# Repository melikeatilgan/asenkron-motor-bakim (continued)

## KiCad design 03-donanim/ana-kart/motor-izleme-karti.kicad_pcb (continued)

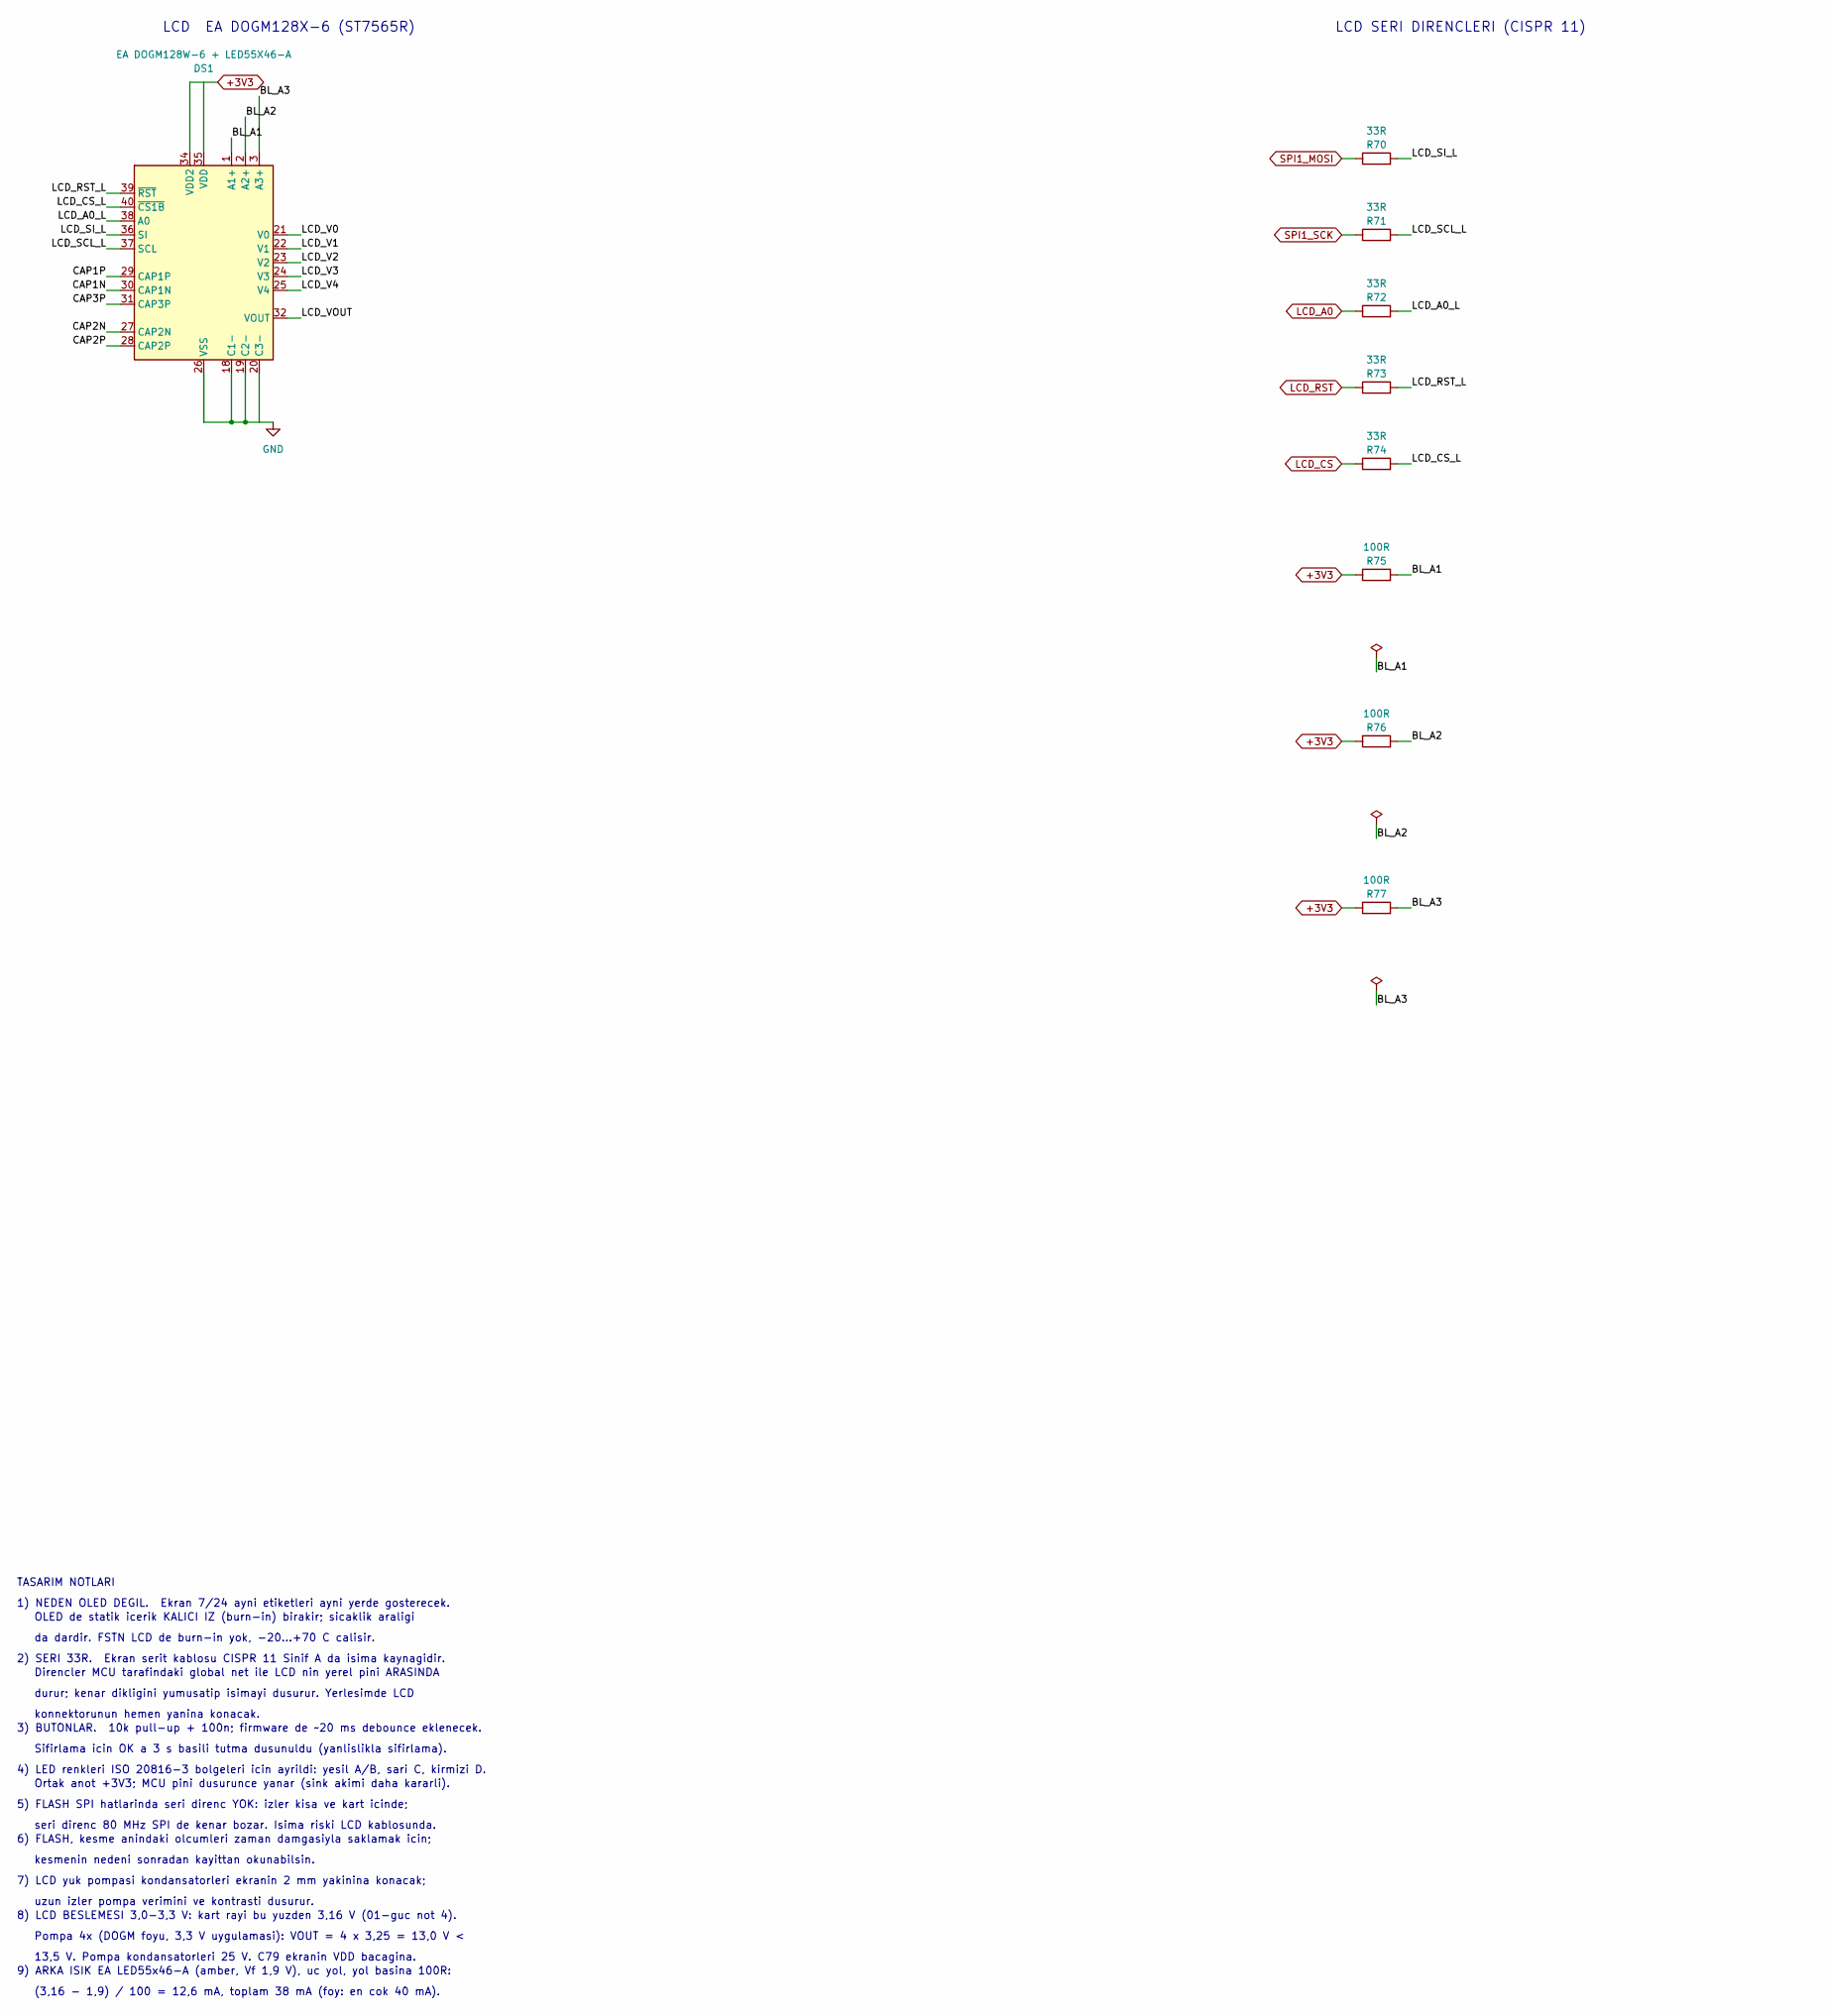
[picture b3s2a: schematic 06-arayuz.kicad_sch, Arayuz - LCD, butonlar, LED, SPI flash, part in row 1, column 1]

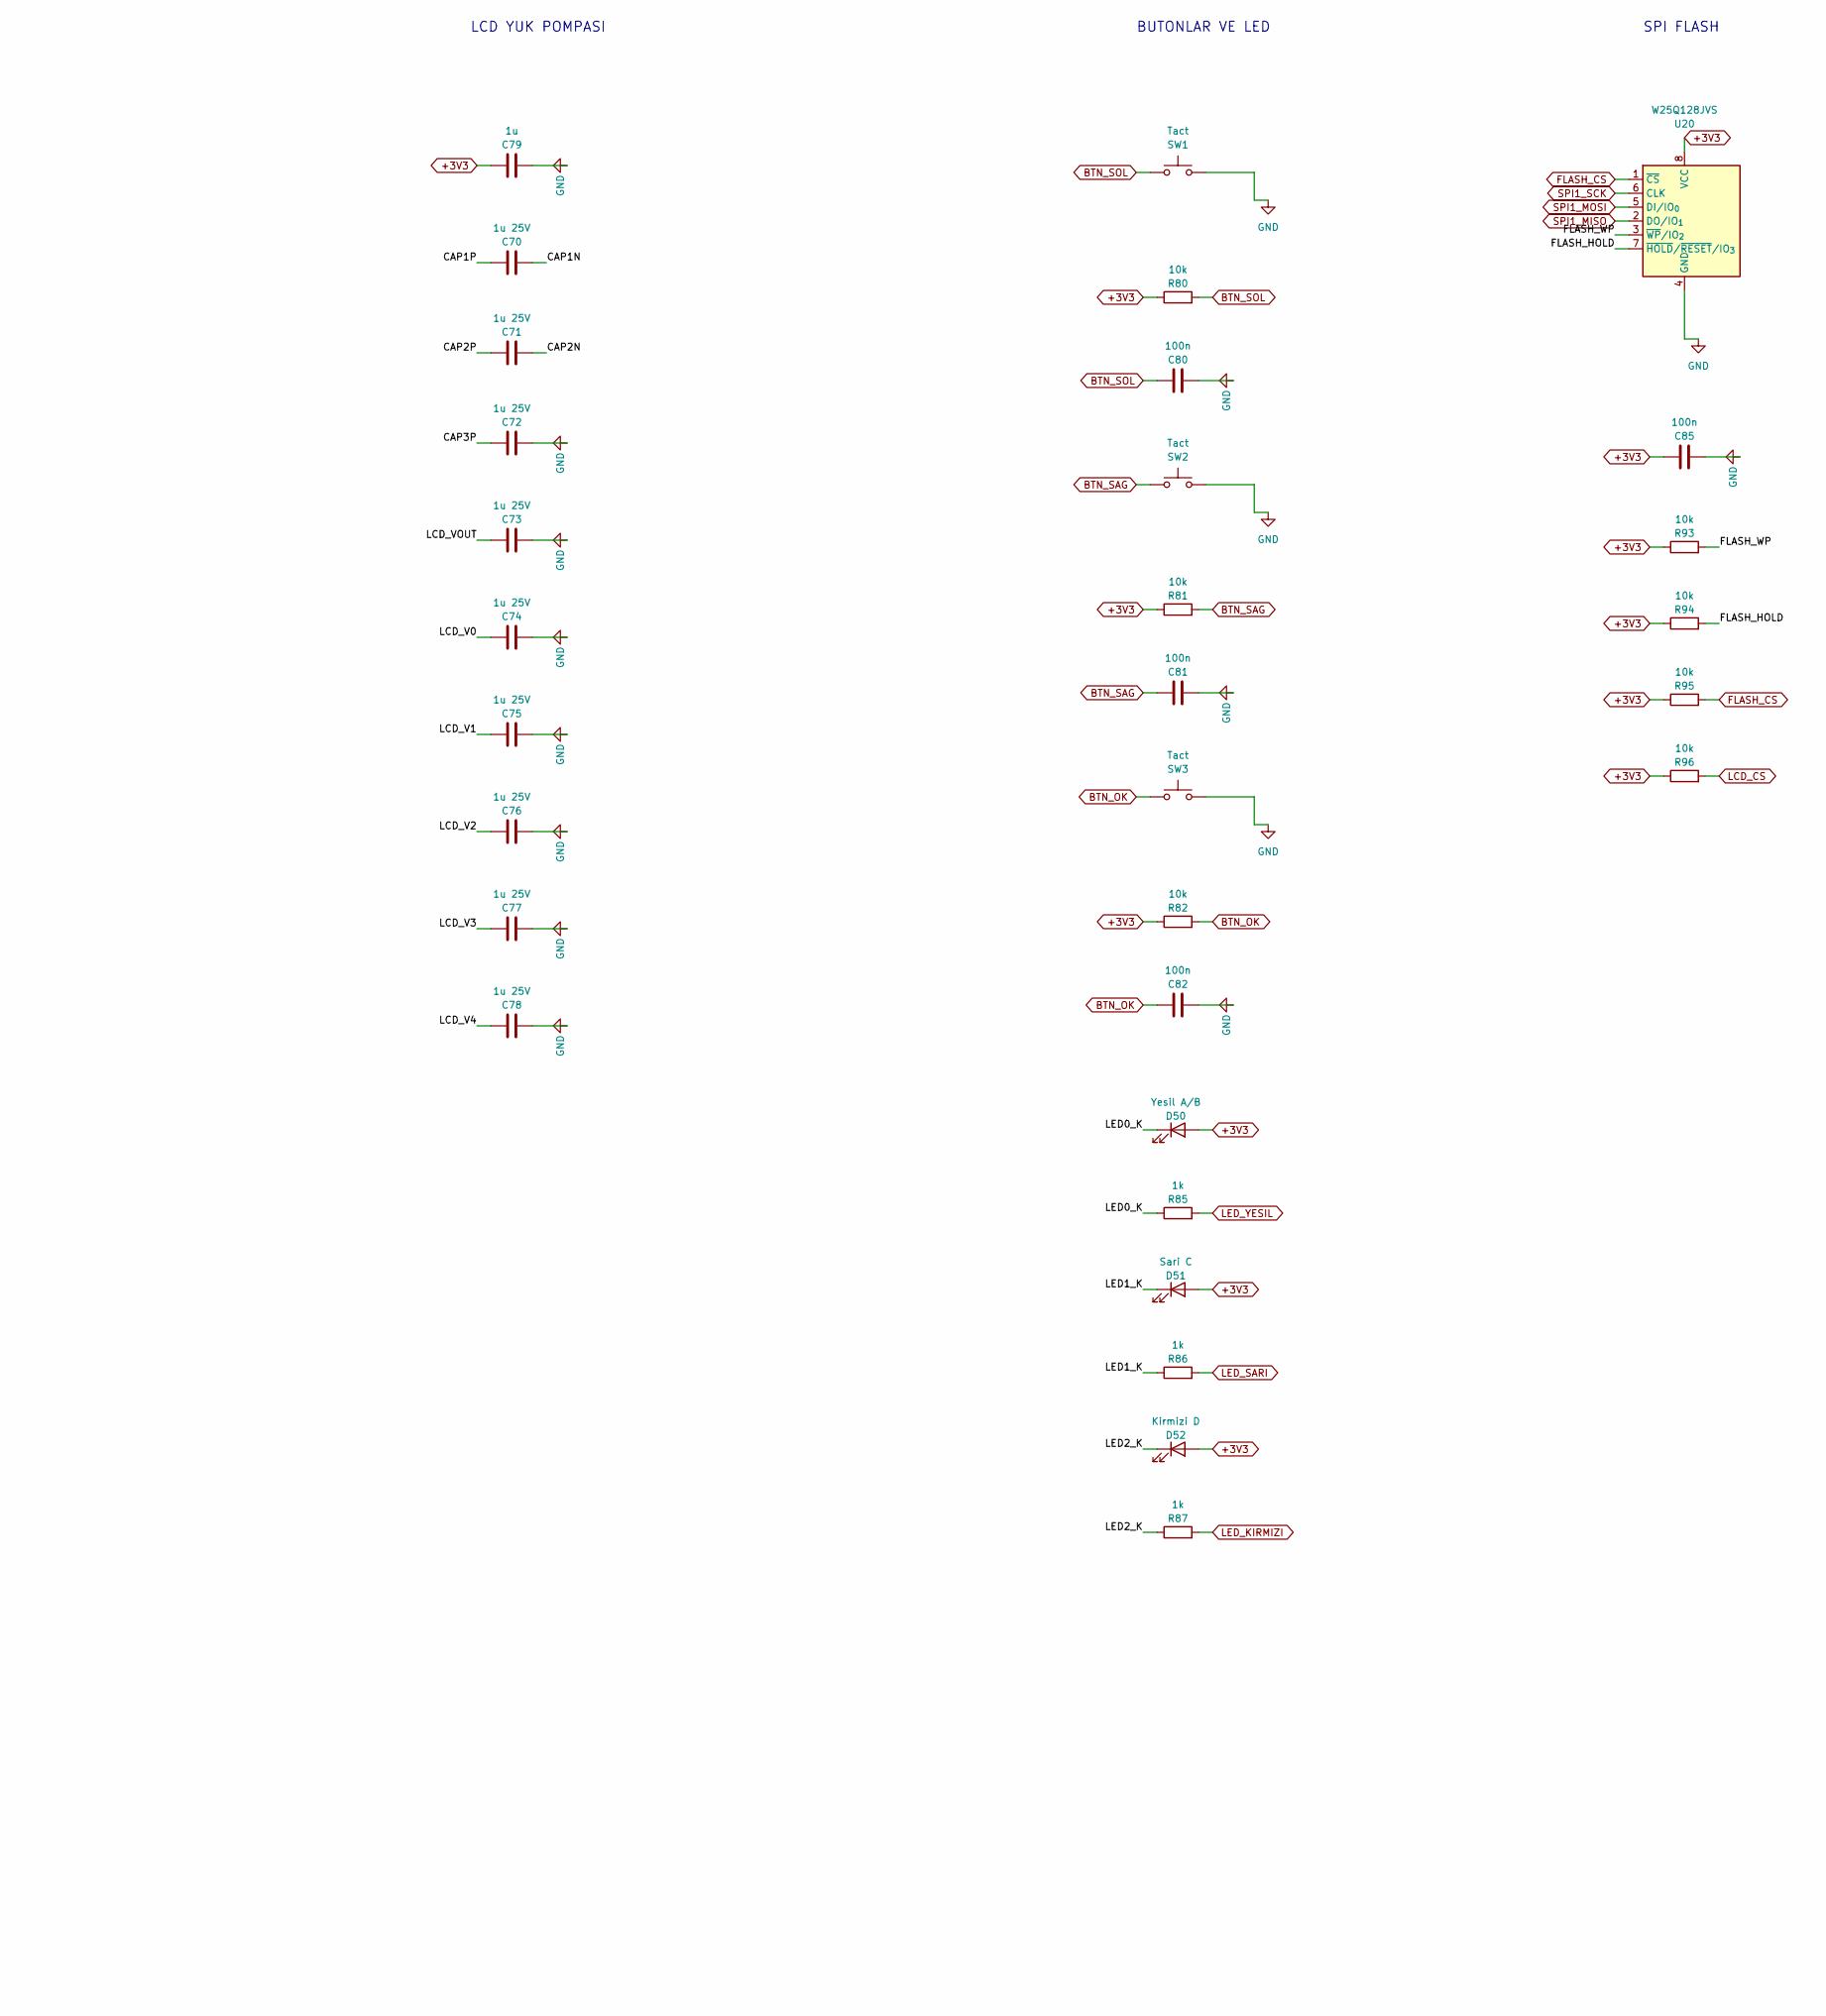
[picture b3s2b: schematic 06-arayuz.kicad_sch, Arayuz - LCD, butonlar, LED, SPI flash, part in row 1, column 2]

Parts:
C70, C71, C72, C73, C74, C75, C76, C77, C78: 1u 25V; C_0805_2012Metric
C79: 1u; C_0805_2012Metric
C80, C81, C82, C85: 100n; C_0805_2012Metric
D50: Yesil A/B; LED_0805_2012Metric
D51: Sari C; LED_0805_2012Metric
D52: Kirmizi D; LED_0805_2012Metric
DS1: EA DOGM128W-6 + LED55X46-A; EA_DOGM128-6
R70, R71, R72, R73, R74: 33R; R_0805_2012Metric
R75, R76, R77: 100R; R_0805_2012Metric
R80, R81, R82, R93, R94, R95, R96: 10k; R_0805_2012Metric
R85, R86, R87: 1k; R_0805_2012Metric
SW1, SW2, SW3: Tact; SW_SPST_PTS645Sx43SMTR92
U20: W25Q128JVS; SOIC-8_3.9x4.9mm_P1.27mm

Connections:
+3V3: C79.1, C85.1, D50.2 (A), D51.2 (A), D52.2 (A), DS1.34 (VDD2), DS1.35 (VDD), R75.1, R76.1, R77.1, R80.1, R81.1, R82.1, R93.1, R94.1, R95.1, R96.1, U20.8 (VCC); also elsewhere on the board
/06-arayuz/BL_A1: DS1.1 (A1+), R75.2
/06-arayuz/BL_A2: DS1.2 (A2+), R76.2
/06-arayuz/BL_A3: DS1.3 (A3+), R77.2
/06-arayuz/CAP1N: C70.2, DS1.30 (CAP1N)
/06-arayuz/CAP1P: C70.1, DS1.29 (CAP1P)
/06-arayuz/CAP2N: C71.2, DS1.27 (CAP2N)
/06-arayuz/CAP2P: C71.1, DS1.28 (CAP2P)
/06-arayuz/CAP3P: C72.1, DS1.31 (CAP3P)
/06-arayuz/FLASH_HOLD: R94.2, U20.7 (~HOLD/~RESET/IO_{3})
/06-arayuz/FLASH_WP: R93.2, U20.3 (~WP/IO_{2})
/06-arayuz/LCD_A0_L: DS1.38 (A0), R72.2
/06-arayuz/LCD_CS_L: DS1.40 (~CS1B), R74.2
/06-arayuz/LCD_RST_L: DS1.39 (~RST), R73.2
/06-arayuz/LCD_SCL_L: DS1.37 (SCL), R71.2
/06-arayuz/LCD_SI_L: DS1.36 (SI), R70.2
/06-arayuz/LCD_V0: C74.1, DS1.21 (V0)
/06-arayuz/LCD_V1: C75.1, DS1.22 (V1)
/06-arayuz/LCD_V2: C76.1, DS1.23 (V2)
/06-arayuz/LCD_V3: C77.1, DS1.24 (V3)
/06-arayuz/LCD_V4: C78.1, DS1.25 (V4)
/06-arayuz/LCD_VOUT: C73.1, DS1.32 (VOUT)
/06-arayuz/LED0_K: D50.1 (K), R85.1
/06-arayuz/LED1_K: D51.1 (K), R86.1
/06-arayuz/LED2_K: D52.1 (K), R87.1
BTN_OK: C82.1, R82.2, SW3.1; also elsewhere on the board
BTN_SAG: C81.1, R81.2, SW2.1; also elsewhere on the board
BTN_SOL: C80.1, R80.2, SW1.1; also elsewhere on the board
FLASH_CS: R95.2, U20.1 (~CS); also elsewhere on the board
GND: C72.2, C73.2, C74.2, C75.2, C76.2, C77.2, C78.2, C79.2, C80.2, C81.2, C82.2, C85.2, DS1.18 (C1-), DS1.19 (C2-), DS1.20 (C3-), DS1.26 (VSS), DS1.33 (VSS), SW1.2, SW2.2, SW3.2, U20.4 (GND); also elsewhere on the board
LCD_A0: R72.1; also elsewhere on the board
LCD_CS: R74.1, R96.2; also elsewhere on the board
LCD_RST: R73.1; also elsewhere on the board
LED_KIRMIZI: R87.2; also elsewhere on the board
LED_SARI: R86.2; also elsewhere on the board
LED_YESIL: R85.2; also elsewhere on the board
SPI1_MISO: U20.2 (DO/IO_{1}); also elsewhere on the board
SPI1_MOSI: R70.1, U20.5 (DI/IO_{0}); also elsewhere on the board
SPI1_SCK: R71.1, U20.6 (CLK); also elsewhere on the board

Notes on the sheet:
SPI FLASH
seri direnc 80 MHz SPI de kenar bozar. Isima riski LCD kablosunda.
TASARIM NOTLARI
3) BUTONLAR. 10k pull-up + 100n; firmware de ~20 ms debounce eklenecek.
uzun izler pompa verimini ve kontrasti dusurur.
7) LCD yuk pompasi kondansatorleri ekranin 2 mm yakinina konacak;
9) ARKA ISIK EA LED55x46-A (amber, Vf 1,9 V), uc yol, yol basina 100R:
13,5 V. Pompa kondansatorleri 25 V. C79 ekranin VDD bacagina.
1) NEDEN OLED DEGIL. Ekran 7/24 ayni etiketleri ayni yerde gosterecek.
LCD SERI DIRENCLERI (CISPR 11)
8) LCD BESLEMESI 3,0-3,3 V: kart rayi bu yuzden 3,16 V (01-guc not 4).
Ortak anot +3V3; MCU pini dusurunce yanar (sink akimi daha kararli).
LCD EA DOGM128X-6 (ST7565R)
Sifirlama icin OK a 3 s basili tutma dusunuldu (yanlislikla sifirlama).
Direncler MCU tarafindaki global net ile LCD nin yerel pini ARASINDA
konnektorunun hemen yanina konacak.
kesmenin nedeni sonradan kayittan okunabilsin.
5) FLASH SPI hatlarinda seri direnc YOK: izler kisa ve kart icinde;
Pompa 4x (DOGM foyu, 3,3 V uygulamasi): VOUT = 4 x 3,25 = 13,0 V <
LCD YUK POMPASI
BUTONLAR VE LED
4) LED renkleri ISO 20816-3 bolgeleri icin ayrildi: yesil A/B, sari C, kirmizi D.
2) SERI 33R. Ekran serit kablosu CISPR 11 Sinif A da isima kaynagidir.
durur; kenar dikligini yumusatip isimayi dusurur. Yerlesimde LCD
OLED de statik icerik KALICI IZ (burn-in) birakir; sicaklik araligi
6) FLASH, kesme anindaki olcumleri zaman damgasiyla saklamak icin;
(3,16 - 1,9) / 100 = 12,6 mA, toplam 38 mA (foy: en cok 40 mA).
da dardir. FSTN LCD de burn-in yok, -20...+70 C calisir.

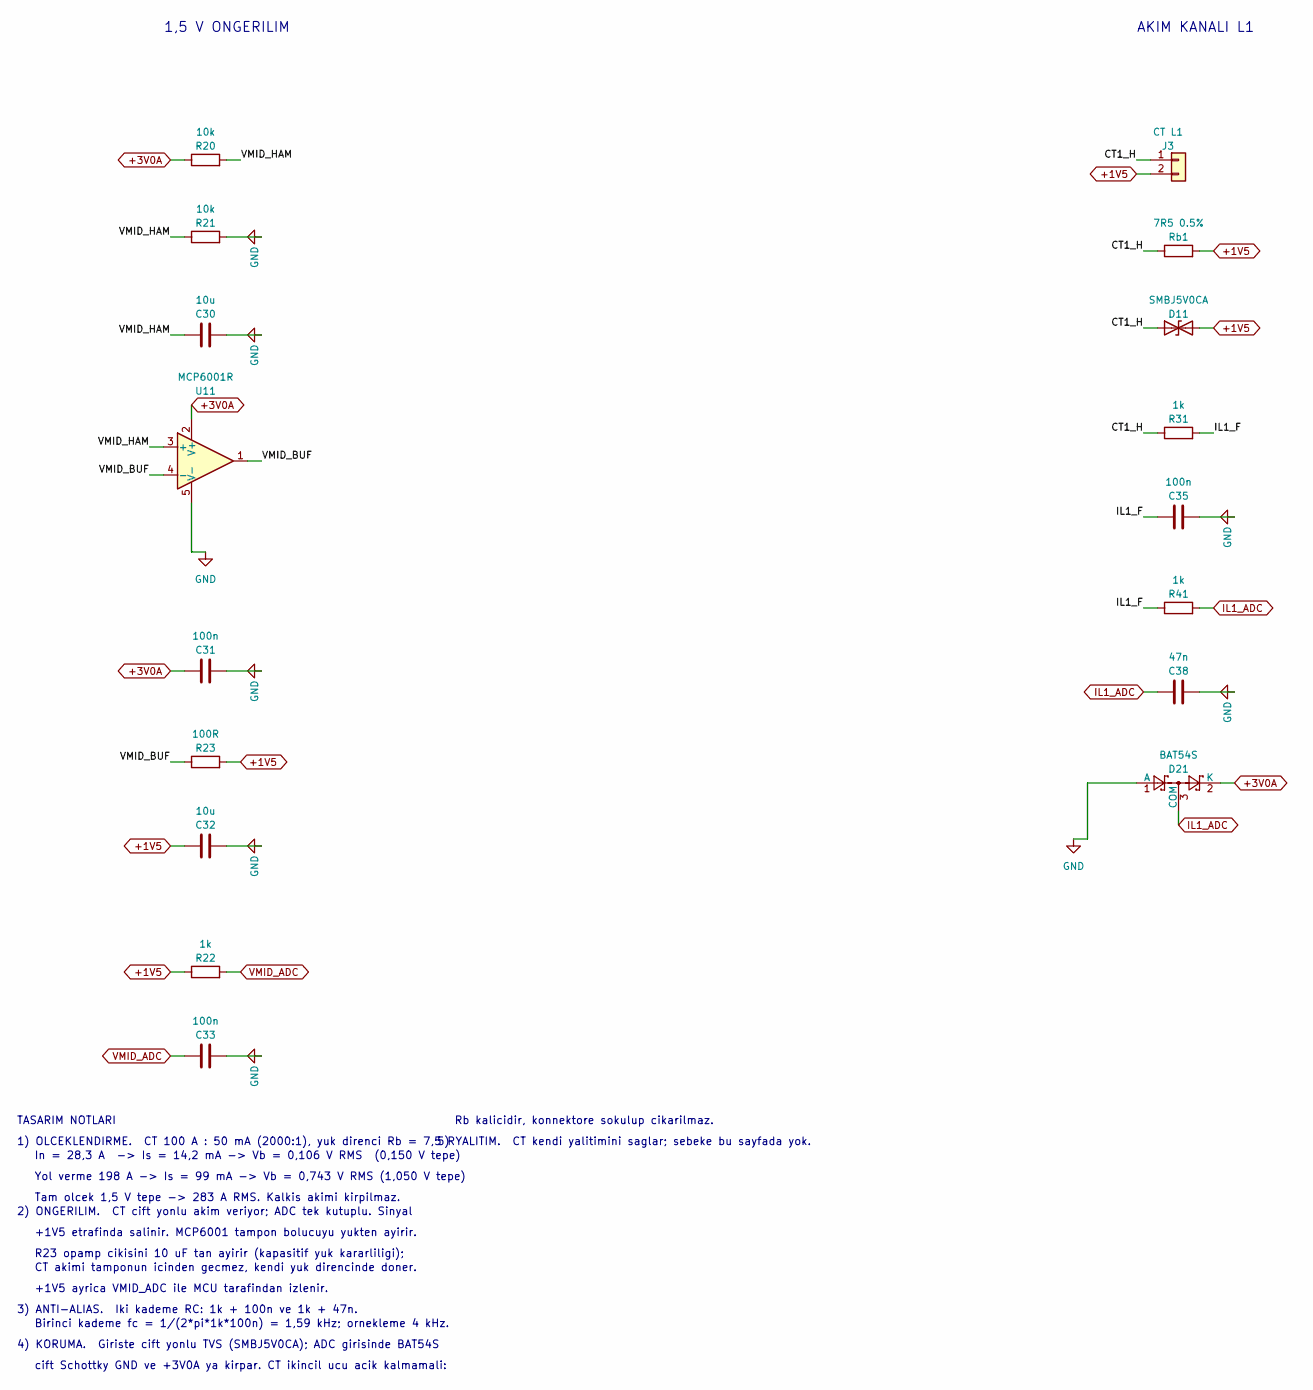
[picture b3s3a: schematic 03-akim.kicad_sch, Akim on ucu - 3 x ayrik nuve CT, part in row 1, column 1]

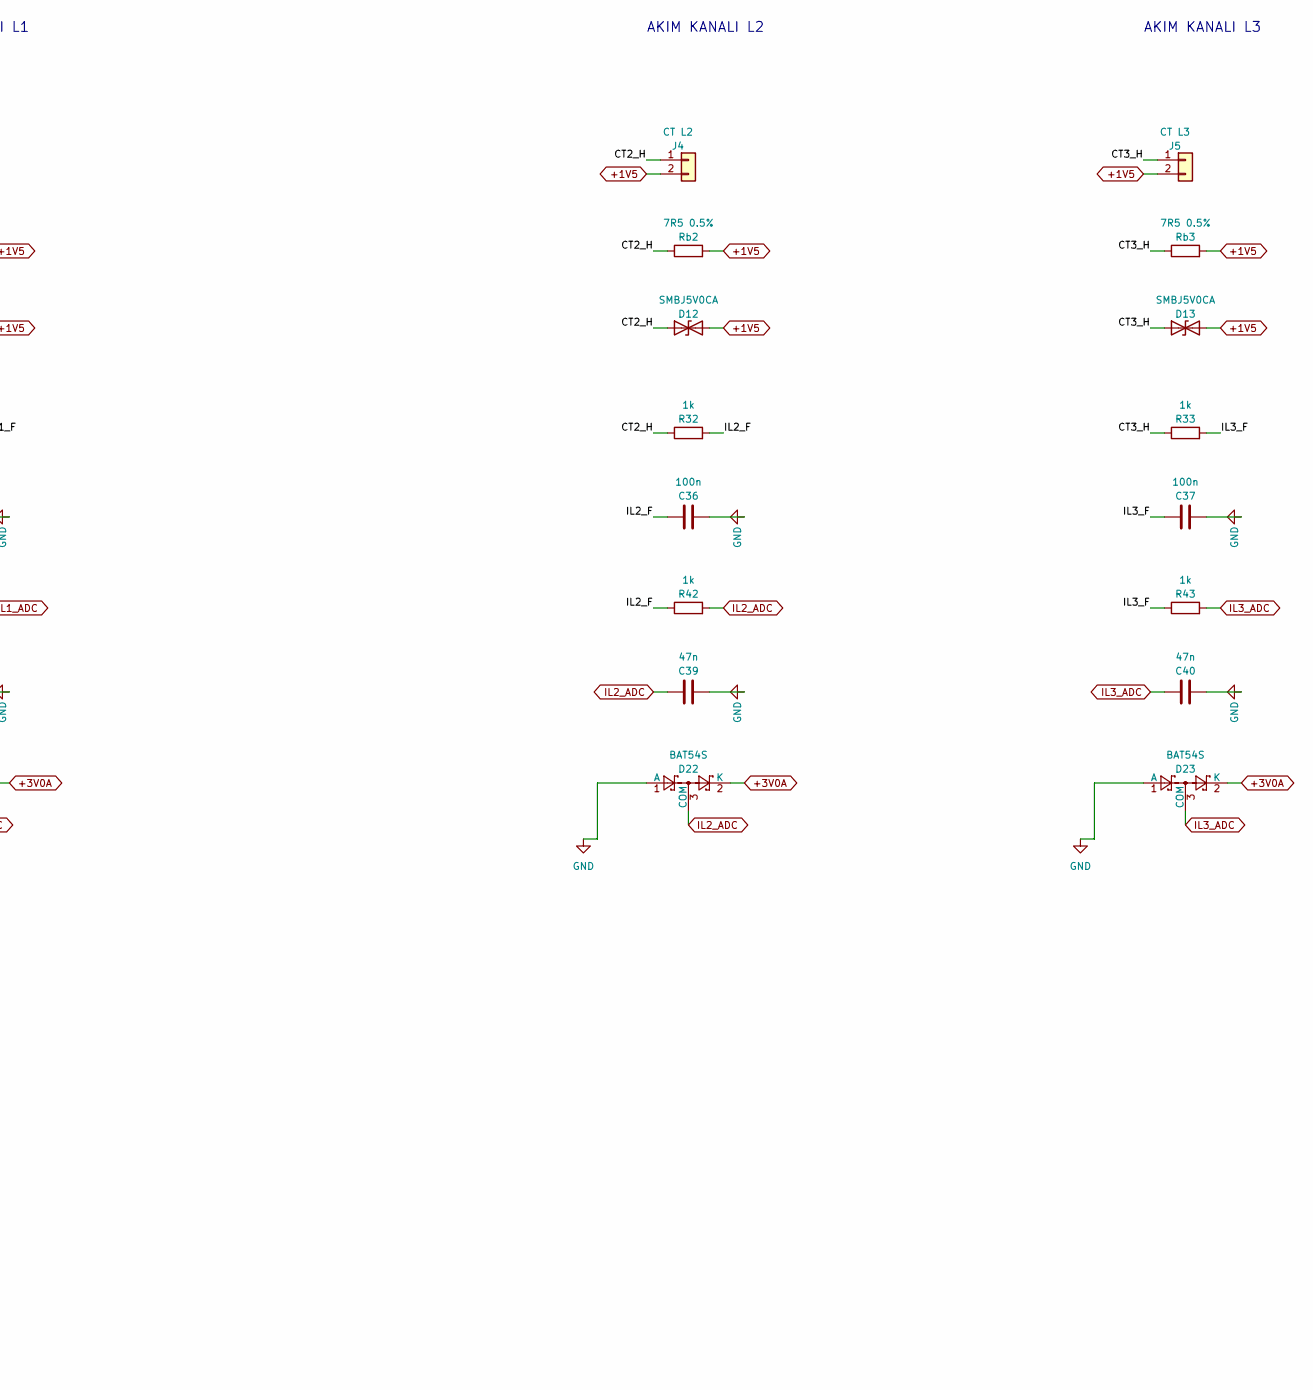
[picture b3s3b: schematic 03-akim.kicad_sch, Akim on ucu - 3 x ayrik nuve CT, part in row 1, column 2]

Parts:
C30, C32: 10u; C_1206_3216Metric
C31, C33, C35, C36, C37: 100n; C_0805_2012Metric
C38, C39, C40: 47n; C_0805_2012Metric
D11, D12, D13: SMBJ5V0CA; D_SMB
D21, D22, D23: BAT54S; SOT-23
J3: CT L1; TerminalBlock_Phoenix_MPT-0,5-2-2.54_1x02_P2.54mm_Horizontal
J4: CT L2; TerminalBlock_Phoenix_MPT-0,5-2-2.54_1x02_P2.54mm_Horizontal
J5: CT L3; TerminalBlock_Phoenix_MPT-0,5-2-2.54_1x02_P2.54mm_Horizontal
R20, R21: 10k; R_0805_2012Metric
R22, R31, R32, R33, R41, R42, R43: 1k; R_0805_2012Metric
R23: 100R; R_0805_2012Metric
Rb1, Rb2, Rb3: 7R5 0.5%; R_0805_2012Metric
U11: MCP6001R; SOT-23-5

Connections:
+1V5: C32.1, D11.2 (A2), D12.2 (A2), D13.2 (A2), J3.2, J4.2, J5.2, R22.1, R23.2, Rb1.2, Rb2.2, Rb3.2
+3V0A: C31.1, D21.2 (K), D22.2 (K), D23.2 (K), R20.1, U11.2 (V+); also elsewhere on the board
/03-akim/CT1_H: D11.1 (A1), J3.1, R31.1, Rb1.1
/03-akim/CT2_H: D12.1 (A1), J4.1, R32.1, Rb2.1
/03-akim/CT3_H: D13.1 (A1), J5.1, R33.1, Rb3.1
/03-akim/IL1_F: C35.1, R31.2, R41.1
/03-akim/IL2_F: C36.1, R32.2, R42.1
/03-akim/IL3_F: C37.1, R33.2, R43.1
/03-akim/VMID_BUF: R23.1, U11.1, U11.4 (-)
/03-akim/VMID_HAM: C30.1, R20.2, R21.1, U11.3 (+)
GND: C30.2, C31.2, C32.2, C33.2, C35.2, C36.2, C37.2, C38.2, C39.2, C40.2, D21.1 (A), D22.1 (A), D23.1 (A), R21.2, U11.5 (V-); also elsewhere on the board
IL1_ADC: C38.1, D21.3 (COM), R41.2; also elsewhere on the board
IL2_ADC: C39.1, D22.3 (COM), R42.2; also elsewhere on the board
IL3_ADC: C40.1, D23.3 (COM), R43.2; also elsewhere on the board
VMID_ADC: C33.1, R22.2; also elsewhere on the board

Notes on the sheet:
Yol verme 198 A -> Is = 99 mA -> Vb = 0,743 V RMS (1,050 V tepe)
In = 28,3 A -> Is = 14,2 mA -> Vb = 0,106 V RMS (0,150 V tepe)
+1V5 etrafinda salinir. MCP6001 tampon bolucuyu yukten ayirir.
AKIM KANALI L1
cift Schottky GND ve +3V0A ya kirpar. CT ikincil ucu acik kalmamali:
AKIM KANALI L2
Tam olcek 1,5 V tepe -> 283 A RMS. Kalkis akimi kirpilmaz.
2) ONGERILIM. CT cift yonlu akim veriyor; ADC tek kutuplu. Sinyal
Rb kalicidir, konnektore sokulup cikarilmaz.
Birinci kademe fc = 1/(2*pi*1k*100n) = 1,59 kHz; ornekleme 4 kHz.
3) ANTI-ALIAS. Iki kademe RC: 1k + 100n ve 1k + 47n.
4) KORUMA. Giriste cift yonlu TVS (SMBJ5V0CA); ADC girisinde BAT54S
+1V5 ayrica VMID_ADC ile MCU tarafindan izlenir.
1,5 V ONGERILIM
5) YALITIM. CT kendi yalitimini saglar; sebeke bu sayfada yok.
1) OLCEKLENDIRME. CT 100 A : 50 mA (2000:1), yuk direnci Rb = 7,5 R
TASARIM NOTLARI
CT akimi tamponun icinden gecmez, kendi yuk direncinde doner.
R23 opamp cikisini 10 uF tan ayirir (kapasitif yuk kararliligi);
AKIM KANALI L3

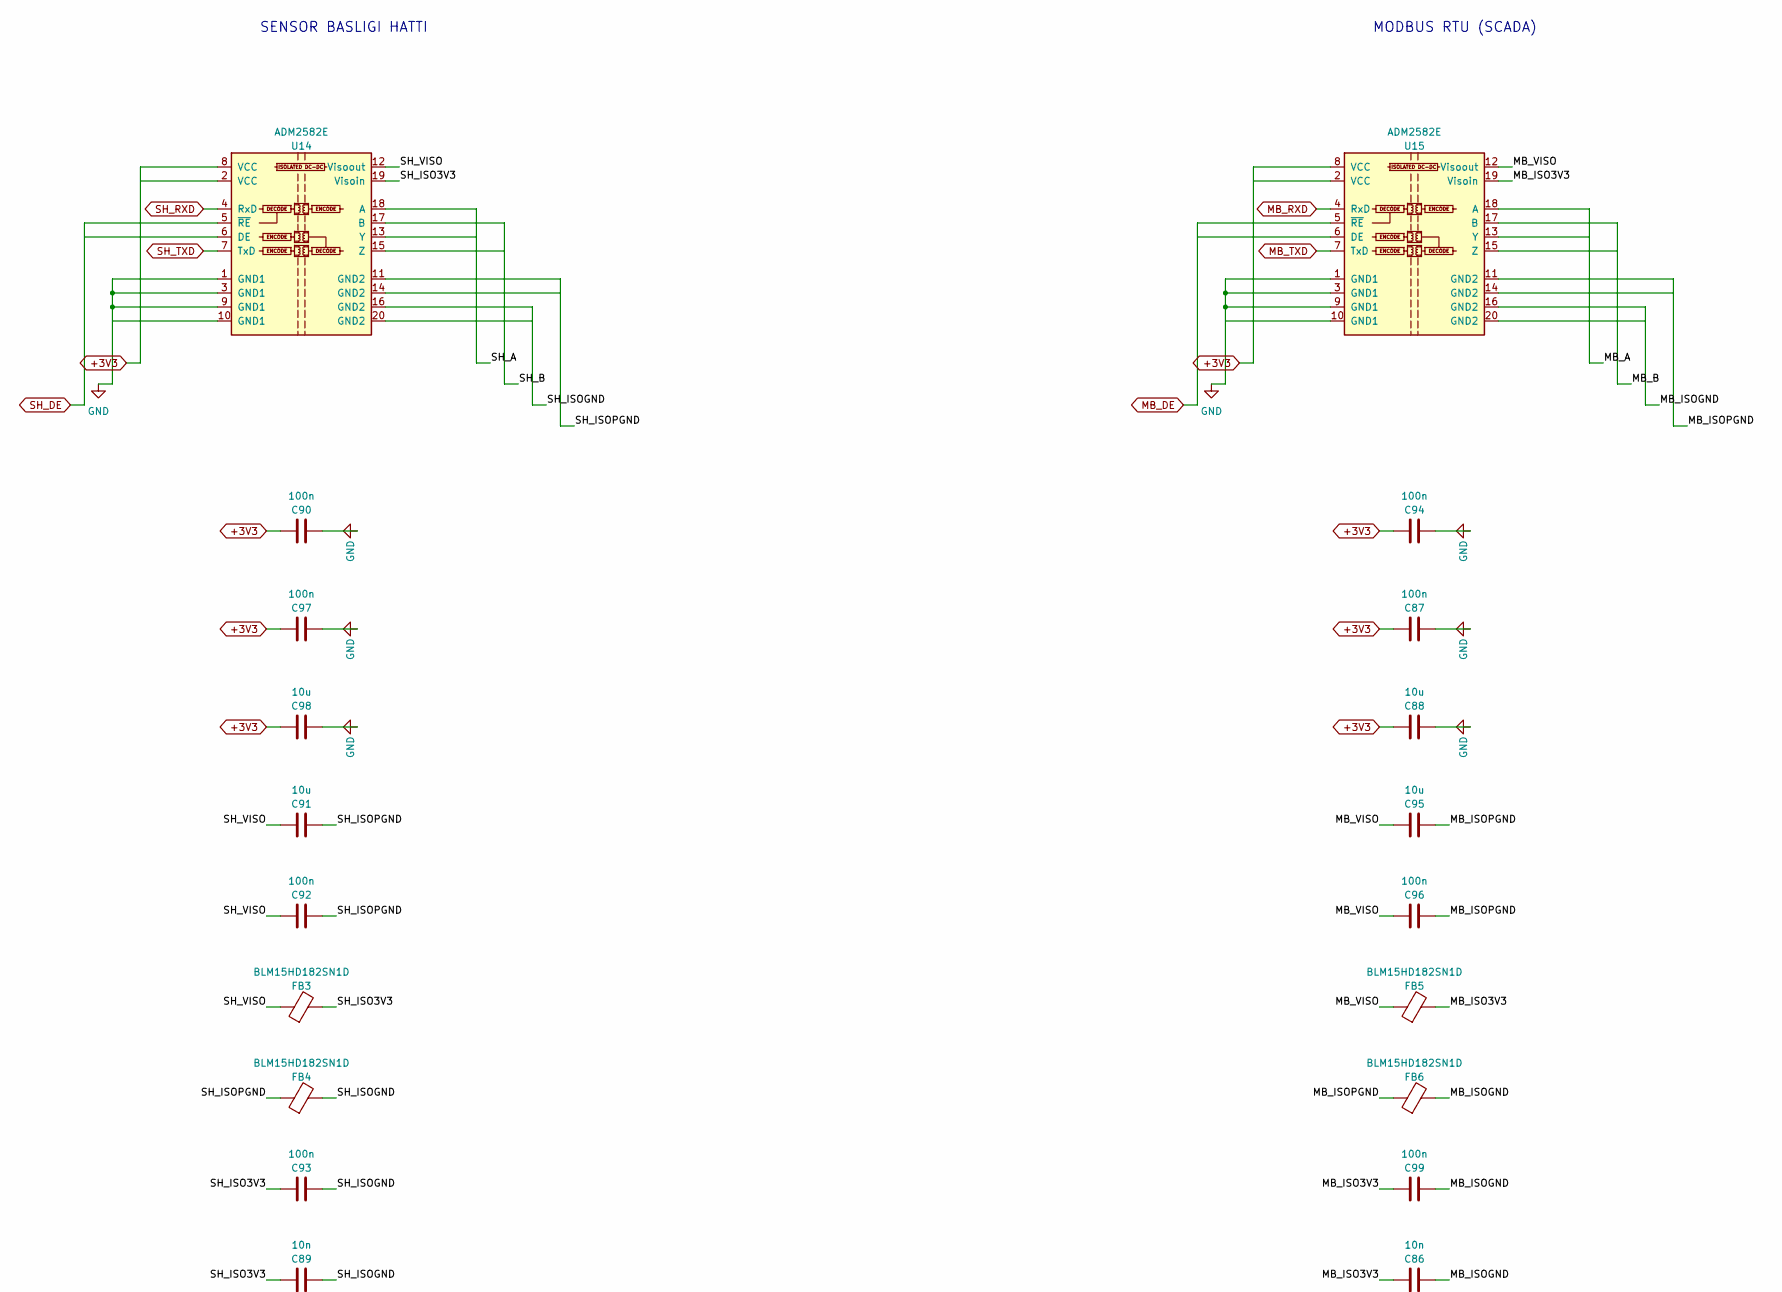
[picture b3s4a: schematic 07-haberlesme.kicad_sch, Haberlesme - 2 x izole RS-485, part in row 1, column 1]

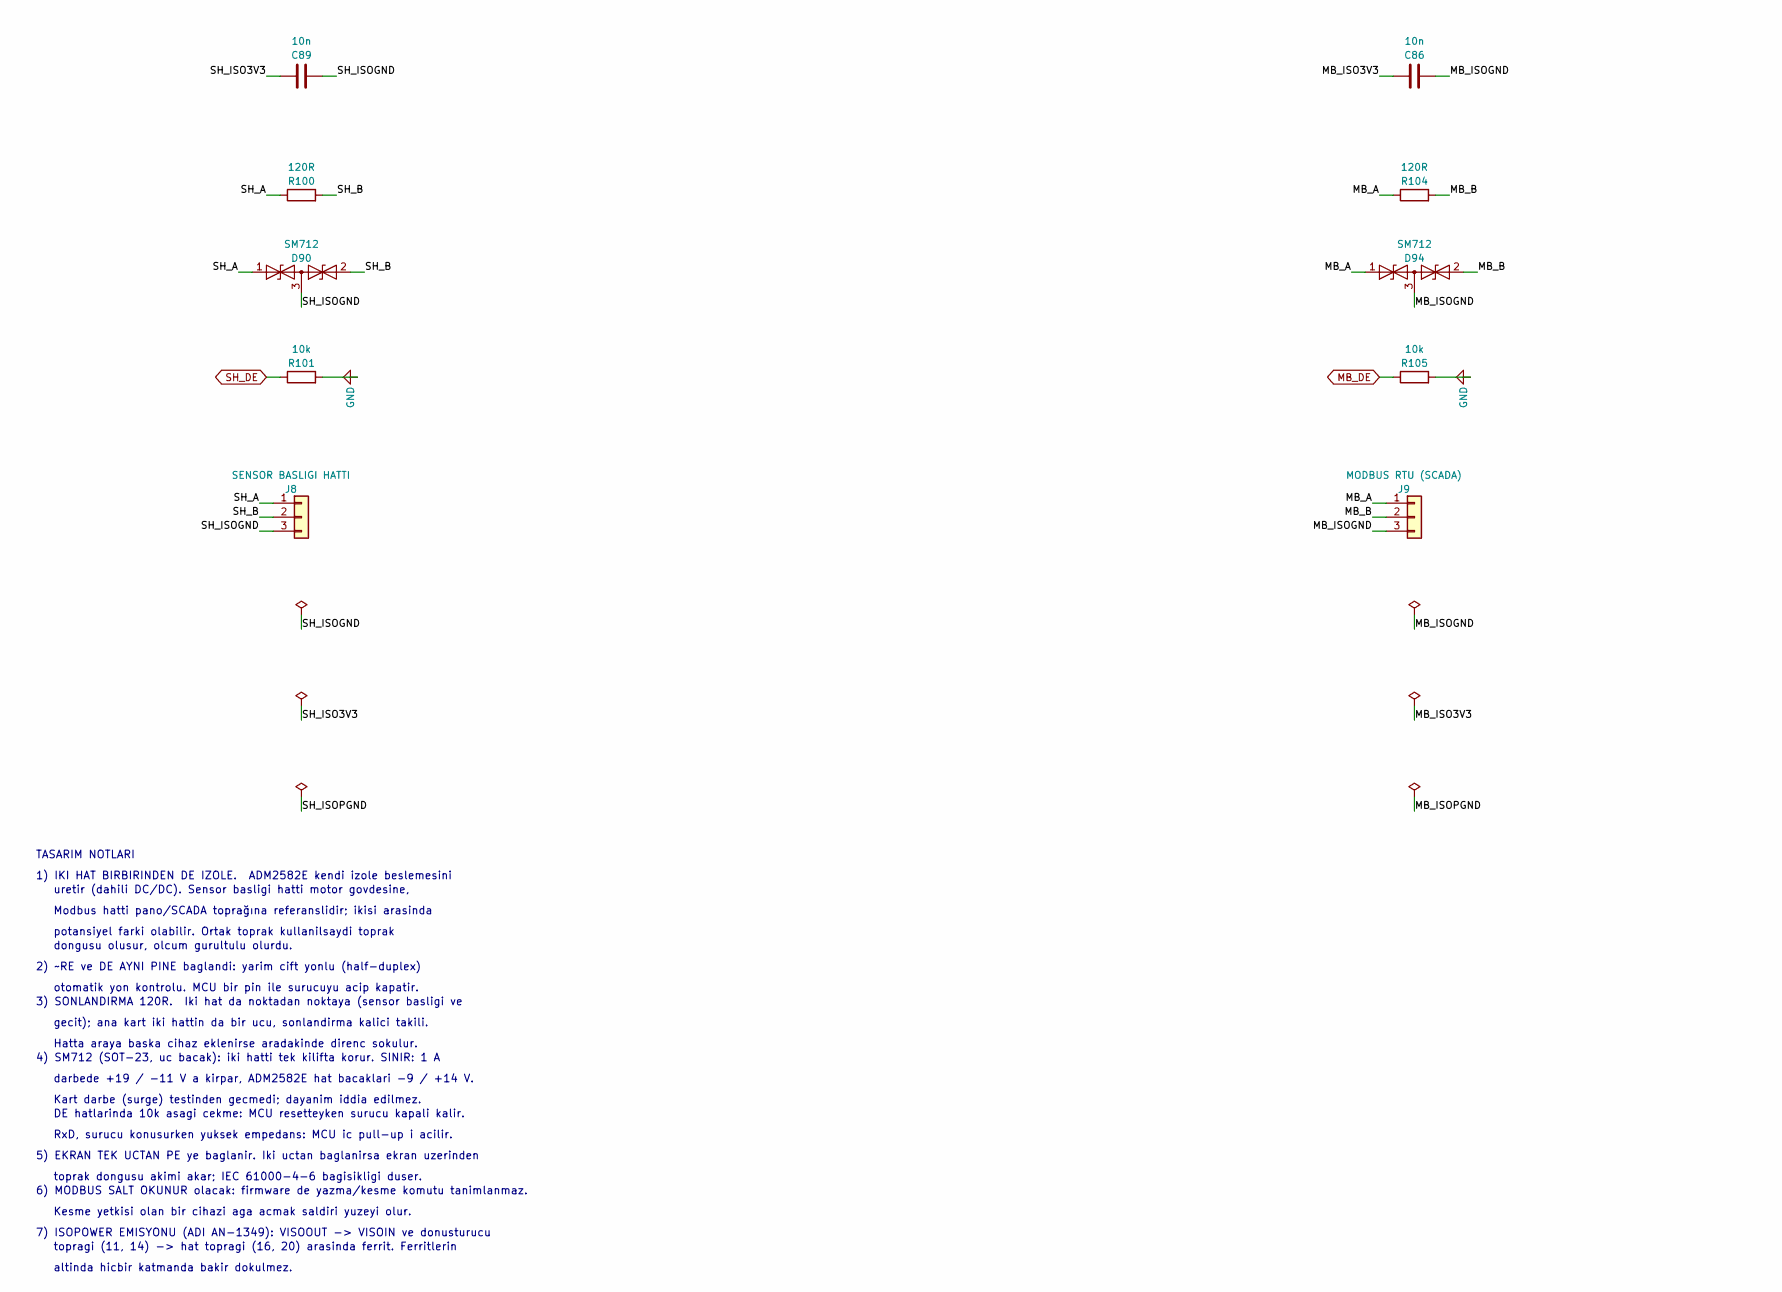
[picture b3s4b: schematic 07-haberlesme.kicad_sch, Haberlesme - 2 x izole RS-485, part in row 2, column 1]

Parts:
C86, C89: 10n; C_0805_2012Metric
C87, C90, C92, C93, C94, C96, C97, C99: 100n; C_0805_2012Metric
C88, C91, C95, C98: 10u; C_1206_3216Metric
D90, D94: SM712; SOT-23
FB3, FB4, FB5, FB6: BLM15HD182SN1D; L_0402_1005Metric
J8: SENSOR BASLIGI HATTI; TerminalBlock_Phoenix_MKDS-1,5-3_1x03_P5.00mm_Horizontal
J9: MODBUS RTU (SCADA); TerminalBlock_Phoenix_MKDS-1,5-3_1x03_P5.00mm_Horizontal
R100, R104: 120R; R_0805_2012Metric
R101, R105: 10k; R_0805_2012Metric
U14, U15: ADM2582E; SOIC-20W_7.5x12.8mm_P1.27mm

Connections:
+3V3: C87.1, C88.1, C90.1, C94.1, C97.1, C98.1, U14.2 (VCC), U14.8 (VCC), U15.2 (VCC), U15.8 (VCC); also elsewhere on the board
/07-haberlesme/MB_A: D94.1 (A1), J9.1, R104.1, U15.13 (Y), U15.18 (A)
/07-haberlesme/MB_B: D94.2 (A2), J9.2, R104.2, U15.15 (Z), U15.17 (B)
/07-haberlesme/MB_ISO3V3: C86.1, C99.1, FB5.2, U15.19 (Visoin)
/07-haberlesme/MB_ISOGND: C86.2, C99.2, D94.3 (common), FB6.2, J9.3, U15.16 (GND2), U15.20 (GND2)
/07-haberlesme/MB_ISOPGND: C95.2, C96.2, FB6.1, U15.11 (GND2), U15.14 (GND2)
/07-haberlesme/MB_VISO: C95.1, C96.1, FB5.1, U15.12 (Visoout)
/07-haberlesme/SH_A: D90.1 (A1), J8.1, R100.1, U14.13 (Y), U14.18 (A)
/07-haberlesme/SH_B: D90.2 (A2), J8.2, R100.2, U14.15 (Z), U14.17 (B)
/07-haberlesme/SH_ISO3V3: C89.1, C93.1, FB3.2, U14.19 (Visoin)
/07-haberlesme/SH_ISOGND: C89.2, C93.2, D90.3 (common), FB4.2, J8.3, U14.16 (GND2), U14.20 (GND2)
/07-haberlesme/SH_ISOPGND: C91.2, C92.2, FB4.1, U14.11 (GND2), U14.14 (GND2)
/07-haberlesme/SH_VISO: C91.1, C92.1, FB3.1, U14.12 (Visoout)
GND: C87.2, C88.2, C90.2, C94.2, C97.2, C98.2, R101.2, R105.2, U14.1 (GND1), U14.3 (GND1), U14.9 (GND1), U14.10 (GND1), U15.1 (GND1), U15.3 (GND1), U15.9 (GND1), U15.10 (GND1); also elsewhere on the board
MB_DE: R105.1, U15.5 (~RE), U15.6 (DE); also elsewhere on the board
MB_RXD: U15.4 (RxD); also elsewhere on the board
MB_TXD: U15.7 (TxD); also elsewhere on the board
SH_DE: R101.1, U14.5 (~RE), U14.6 (DE); also elsewhere on the board
SH_RXD: U14.4 (RxD); also elsewhere on the board
SH_TXD: U14.7 (TxD); also elsewhere on the board

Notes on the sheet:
TASARIM NOTLARI
7) ISOPOWER EMISYONU (ADI AN-1349): VISOOUT -> VISOIN ve donusturucu
Hatta araya baska cihaz eklenirse aradakinde direnc sokulur.
DE hatlarinda 10k asagi cekme: MCU resetteyken surucu kapali kalir.
darbede +19 / -11 V a kirpar, ADM2582E hat bacaklari -9 / +14 V.
gecit); ana kart iki hattin da bir ucu, sonlandirma kalici takili.
dongusu olusur, olcum gurultulu olurdu.
3) SONLANDIRMA 120R. Iki hat da noktadan noktaya (sensor basligi ve
altinda hicbir katmanda bakir dokulmez.
topragi (11, 14) -> hat topragi (16, 20) arasinda ferrit. Ferritlerin
MODBUS RTU (SCADA)
SENSOR BASLIGI HATTI
RxD, surucu konusurken yuksek empedans: MCU ic pull-up i acilir.
uretir (dahili DC/DC). Sensor basligi hatti motor govdesine,
Kesme yetkisi olan bir cihazi aga acmak saldiri yuzeyi olur.
toprak dongusu akimi akar; IEC 61000-4-6 bagisikligi duser.
5) EKRAN TEK UCTAN PE ye baglanir. Iki uctan baglanirsa ekran uzerinden
4) SM712 (SOT-23, uc bacak): iki hatti tek kilifta korur. SINIR: 1 A
potansiyel farki olabilir. Ortak toprak kullanilsaydi toprak
6) MODBUS SALT OKUNUR olacak: firmware de yazma/kesme komutu tanimlanmaz.
otomatik yon kontrolu. MCU bir pin ile surucuyu acip kapatir.
2) ~RE ve DE AYNI PINE baglandi: yarim cift yonlu (half-duplex)
Kart darbe (surge) testinden gecmedi; dayanim iddia edilmez.
Modbus hatti pano/SCADA toprağına referanslidir; ikisi arasinda
1) IKI HAT BIRBIRINDEN DE IZOLE. ADM2582E kendi izole beslemesini
